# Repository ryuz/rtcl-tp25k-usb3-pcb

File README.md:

English version: [README_en.md](README_en.md)

# Tang Primer 25K 用 FT601 + MIPIコネクタ オリジナルベース基板

## 概要

Sipeed社の [Tang Primer 25K](https://wiki.sipeed.com/hardware/en/tang/tang-primer-25k/primer-25k.html) に搭載されている GW5A-LV25MG121 には MIPI D-PHY インターフェースが搭載されており、SoM までは配線が来ているようですが、残念ながら標準の Dock base board ではこのラインが未接続のままになっており、利用することができません。

本プロジェクトでは、MIPI D-PHY ラインを活用できるように 0.5mm ピッチ 22pin のコネクタに引き出したうえで、画像データなどを PC と交換できるように FT601 で USB3.0 接続できるオリジナルベース基板の設計データを提供します。

Tang Primer 25K の SoMボード でもともと使われていなかった MIPI ピンを利用するようにしていますが、特に MIPI を活用しなくとも、USB3.0 で FPGA を使えるようにしたボードとも言えますので、今まで FPGA と PC との接続で UART 程度で止まっていた人に本格的な FPGA 活用への第一歩として利用いただければ幸いです。

また、当方では試しておりませんが、GW5A-LV25MG121 の MIPI D-PHY は双方向ですので、MIPI-DSI など、表示系の実験にも利用できる可能性があります。

## スペック

主な実装内容は以下です。

- Tang-Primer25K-Core 取り付け用コネクタ
- FT601 による USB3.0 接続
- 4レーン MIPI コネクタ (22pin)
- PMOD コネクタ一個
- LED 4個
- プッシュスイッチ2個
- 2極ディップスイッチ
- JTAG 接続用 6pin ヘッダ

JTAG は外部に別途ダウンロードケーブルが必要ですが、[openFPGAloader](https://github.com/trabucayre/openFPGALoader)などを利用する場合は幅広いダウンロードケーブルが利用可能です。

また FT232HL などを利用する場合は、GOWIN EDA の GAO などを使ったデバッグも可能です。

## システムイメージ

### カメラ接続

[Raspberry PI V2 Camera](https://www.raspberrypi.com/documentation/accessories/camera.html) の接続例と、当方作の[RTCL-P3S7-MIPI](https://rtc-lab.com/products/rtcl-cam-p3s7-mipi/)の接続例です。

### JTAG接続

Digilent社の [JTAG-HS２](https://digilent.com/reference/programmers/jtag-hs2/start) の接続例と、秋月電子の[FT232HL ハイスピードUSBシリアル変換モジュール](https://akizukidenshi.com/catalog/g/g106503/) の接続例です。

## 設計データ

### 回路図

回路図は以下です。

- [rtcl-tp25k-usb3_v2.pdf](rtcl-tp25k-usb3_v2.pdf)

### KiCAD 設計データ

rtcl-tp25k-usb3 ディレクトリ以下に KiCAD 10.0 で設計したデータを格納しています。

JLCPCB の `JLC04161H-3313` で製造する想定で設計しています。

### ソフトウェア

下記にて開発中です。

https://github.com/ryuz/rtcl-designs/tree/main/projects/rtcl_tp25k_usb3

## 基板販売

当方で製造したものを[BOOTH](https://rtc-lab.booth.pm/) 及び [BASE](https://rtcl.base.shop/) にて販売中です。

詳細は下記をご覧ください。

https://rtc-lab.com/products/rtcl-design-rtcl_tp25k_usb3/

## 免責事項

本設計データは、研究開発用の試作実験に供するものであり、利用に際して発生した如何なる損害も作者は補償いたしませんので予めご了承ください。

また設計データについてもなんら品質を保証するものではありません。

## ライセンス(License)

本設計データは、[クリエイティブ・コモンズ 表示-非営利 4.0 国際 ライセンス(CC BY-NC 4.0)](https://creativecommons.org/licenses/by-nc/4.0/deed.ja)の下で提供されています。

製造した本基板の無断での販売や配布を行わない限りは、趣味や研究開発用途でご自由にお使いいただく事が出来ます。

また、商用に製造販売を希望される場合は、別途ライセンス契約を作者までご相談ください。[お問い合わせフォーム](https://rtc-lab.com/contact/)などからお問い合わせ頂けます。

## 作者情報

渕上 竜司(Ryuji Fuchikami)
[リアルタイムコンピューティング研究所](https://rtc-lab.com/)

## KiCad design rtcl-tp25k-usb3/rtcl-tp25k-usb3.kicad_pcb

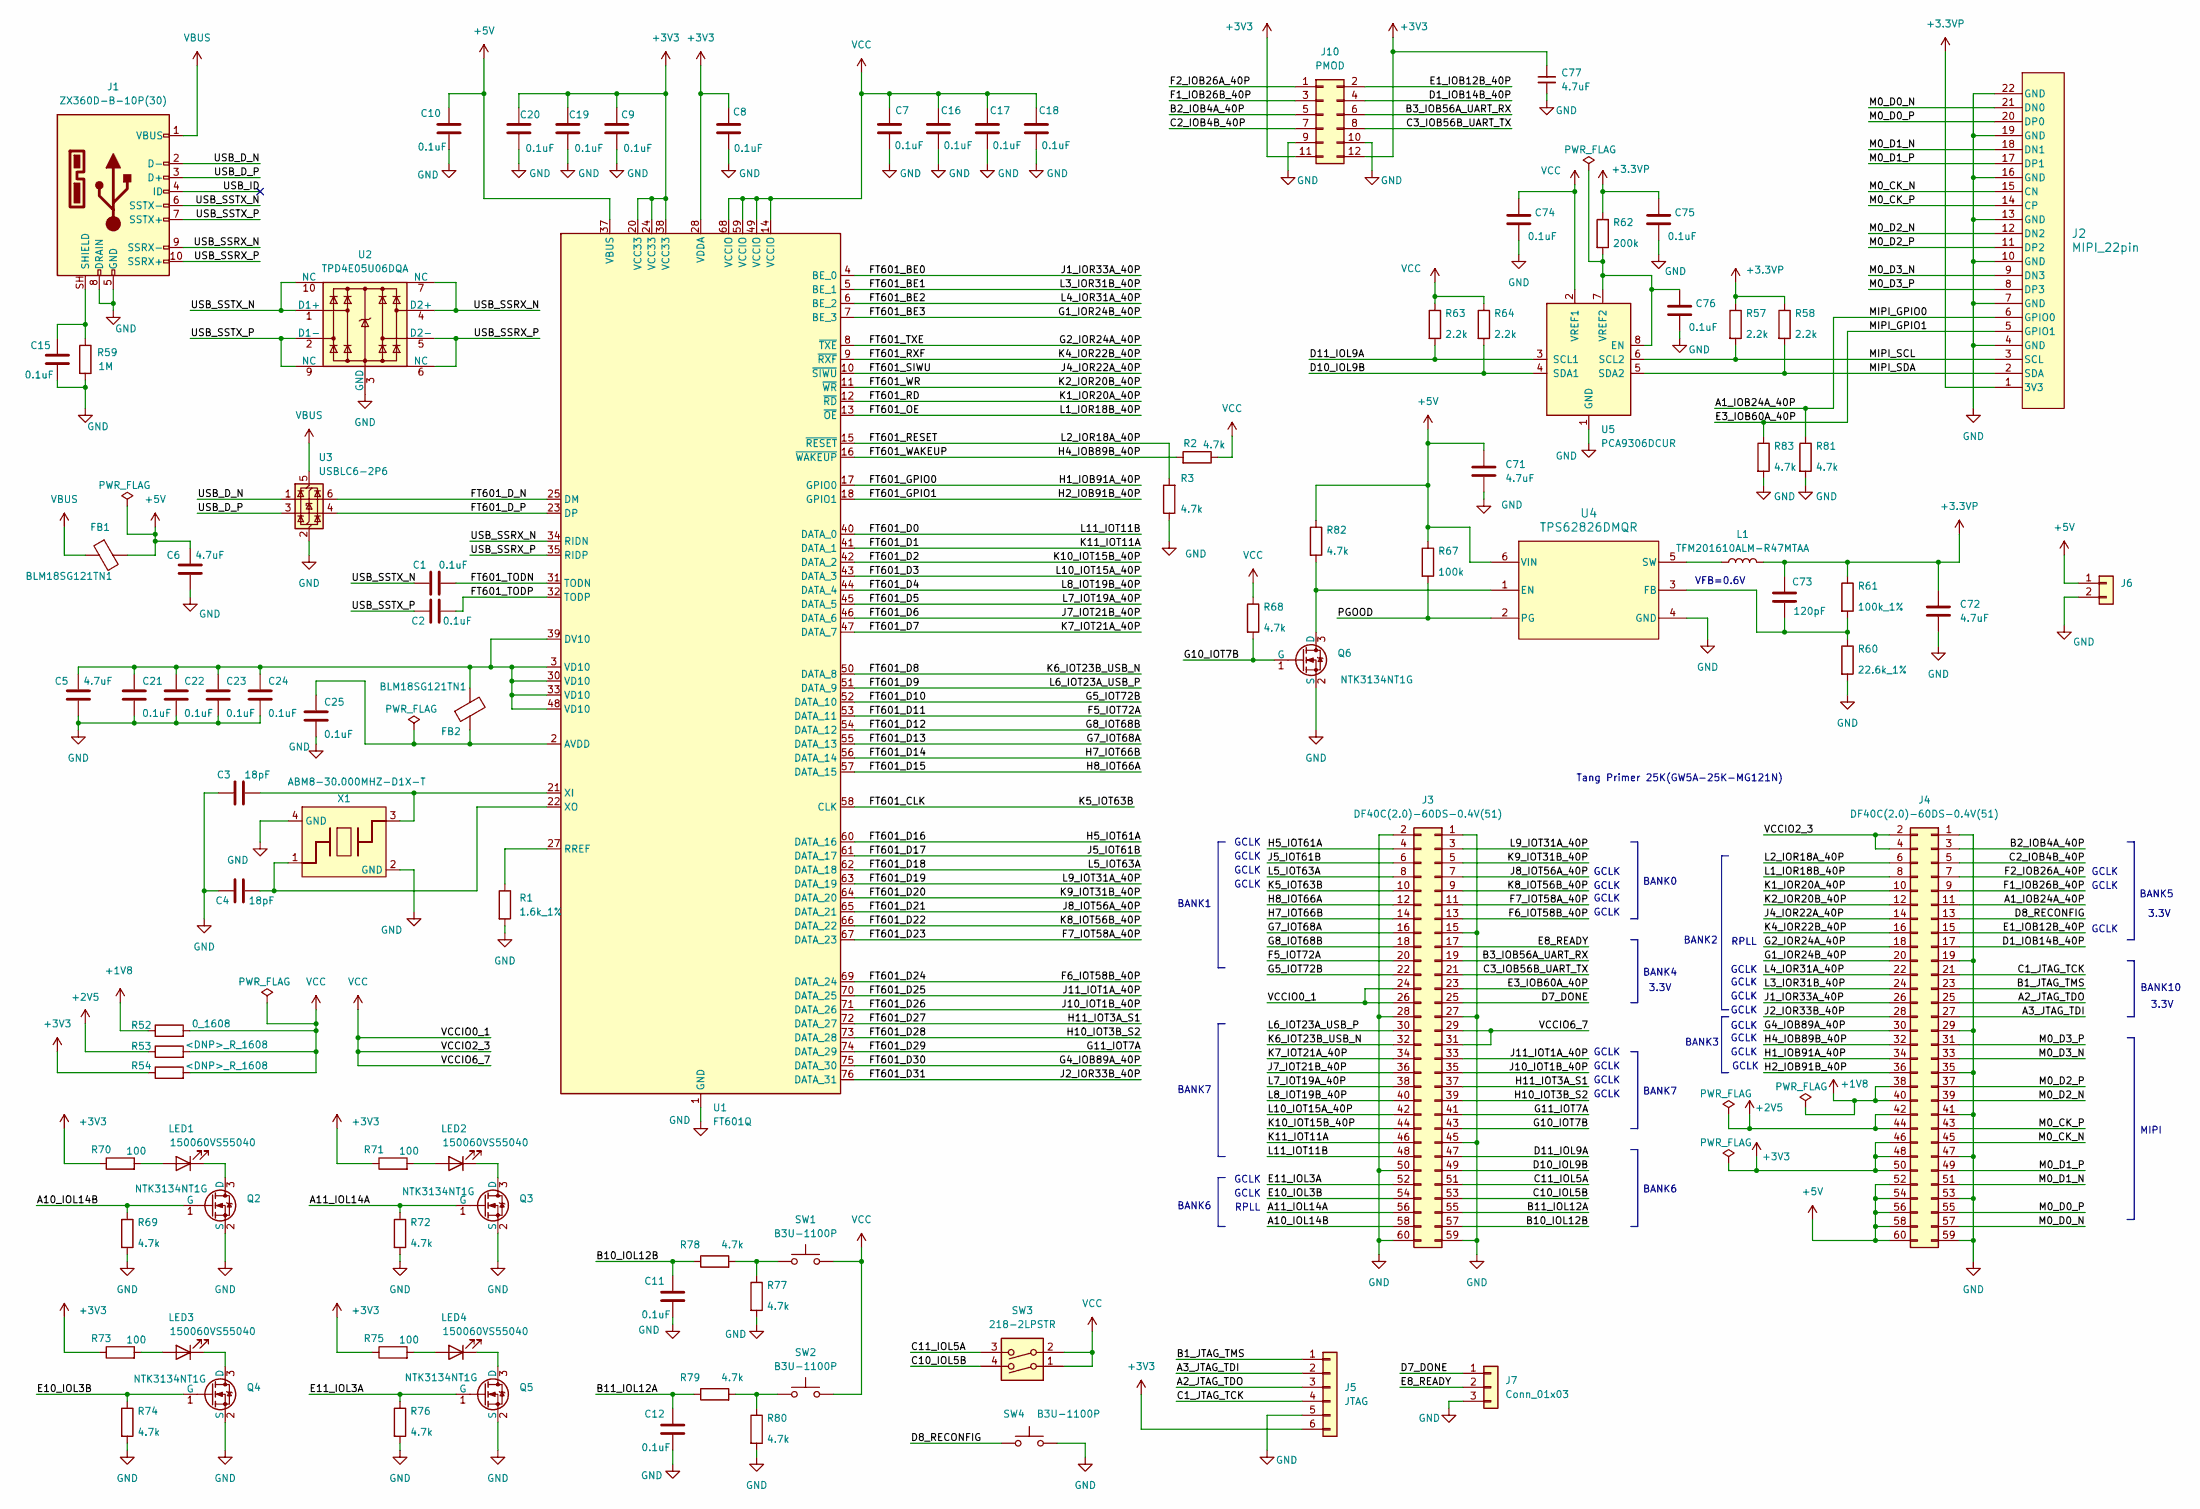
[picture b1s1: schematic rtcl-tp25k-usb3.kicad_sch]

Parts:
C1, C2, C7, C8, C9, C10, C11, C12, C15, C16, C17, C18, C19, C20, C21, C22, C23, C24, C25, C74, C75, C76: 0.1uF; C_0402_1005Metric
C3, C4: 18pF; C_0402_1005Metric
C5, C6, C71, C72, C77: 4.7uF; C_0603_1608Metric
C73: 120pF; C_0402_1005Metric; LCSC C40059
FB1, FB2: BLM18SG121TN1; L_0603_1608Metric; LCSC C113030
J1: ZX360D-B-10P(30); ZX360DB10P30; LCSC C598201
J2: MIPI_22pin; AFC11-S22ICA-00; LCSC C5248019
J3, J4: DF40C(2.0)-60DS-0.4V(51); CONN_DF40C-60DS_HIR; LCSC C3646124
J5: JTAG; PinHeader_1x06_P2.54mm_Vertical; LCSC C6332199
J6: Conn_01x02; PinHeader_1x02_P2.54mm_Vertical
J7: Conn_01x03; PinHeader_1x03_P2.54mm_Vertical
J10: PMOD; PMOD_02x06_2.54mm; LCSC C2897426
L1: TFM201610ALM-R47MTAA; INDC2016X100N; LCSC C501954
LED1, LED2, LED3, LED4: 150060VS55040; LED_0603_1608Metric; LCSC C6390388
Q2, Q3, Q4, Q5, Q6: NTK3134NT1G; SOT_34NT1G_ONS; Part 2SK3018; LCSC C97777
R1: 1.6k_1%; R_0402_1005Metric
R2, R3, R68, R69, R72, R74, R76, R77, R78, R79, R80, R81, R82, R83: 4.7k; R_0402_1005Metric
R52: 0_1608; R_0603_1608Metric_Pad0.98x0.95mm_HandSolder; LCSC C15402
R53, R54: <DNP>_R_1608; R_0603_1608Metric_Pad0.98x0.95mm_HandSolder
R57, R58, R63, R64: 2.2k; R_0402_1005Metric
R59: 1M; R_0402_1005Metric
R60: 22.6k_1%; R_0402_1005Metric
R61: 100k_1%; R_0402_1005Metric
R62: 200k; R_0402_1005Metric
R67: 100k; R_0402_1005Metric
R70, R71, R73, R75: 100; R_0402_1005Metric
SW1, SW2, SW4: B3U-1100P; LCSC C6467298
SW3: 218-2LPSTR; 218-2LP_CTS; LCSC C2961921
U1: FT601Q; QFN-76-1EP_9x9mm_P0.4mm_EP5.81x6.31mm; LCSC C1550513
U2: TPD4E05U06DQA; USON-10_2.5x1.0mm_P0.5mm; LCSC C138714
U3: USBLC6-2P6; SOT-666; LCSC C15999
U4: TPS62826DMQR; DMQ0006A; LCSC C2073319
U5: PCA9306DCUR; VSSOP-8_2.3x2mm_P0.5mm; LCSC C33196
X1: ABM8-30.000MHZ-D1X-T; XTAL_ABM8-30.000MHz-D1X-T; LCSC C1986781

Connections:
+1V8: J4.38, J4.40, R52.1
+2V5: J4.42, J4.44, R53.1
+3.3VP: C72.1, C73.1, C75.1, J2.1 (3V3), L1.2, R57.1, R58.1, R61.1, R62.1
+3V3: C8.2, C9.2, C19.2, C20.2, C77.1, J4.46, J4.48, J4.50, J5.6, J10.11, J10.12, R54.1, R70.1, R71.1, R73.1, R75.1, U1.20 (VCC33), U1.24 (VCC33), U1.28 (VDDA), U1.38 (VCC33)
+5V: C6.2, C10.2, C71.1, FB1.2, J4.52, J4.54, J4.56, J4.58, J4.60, J6.1, R67.1, R82.1, U1.37 (VBUS), U4.6 (VIN)
/A1_IOB24A_40P: J2.6 (GPIO0), J4.11, R81.1
/A2_JTAG_TDO: J4.25, J5.3
/A3_JTAG_TDI: J4.27, J5.2
/A10_IOL14B: J3.58, Q2.1 (G), R69.1
/A11_IOL14A: J3.56, Q3.1 (G), R72.1
/B1_JTAG_TMS: J4.23, J5.1
/B2_IOB4A_40P: J4.3, J10.5
/B3_IOB56A_UART_RX: J3.19, J10.6
/B10_IOL12B: C11.2, J3.57, R78.1
/B11_IOL12A: C12.2, J3.55, R79.1
/C1_JTAG_TCK: J4.21, J5.4
/C2_IOB4B_40P: J4.5, J10.7
/C3_IOB56B_UART_TX: J3.21, J10.8
/C10_IOL5B: J3.53, SW3.4
/C11_IOL5A: J3.51, SW3.3
/D1_IOB14B_40P: J4.17, J10.4
/D7_DONE: J3.25, J7.1
/D8_RECONFIG: J4.13, SW4.1
/D10_IOL9B: J3.49, R64.2, U5.4 (SDA1)
/D11_IOL9A: J3.47, R63.2, U5.3 (SCL1)
/E1_IOB12B_40P: J4.15, J10.2
/E3_IOB60A_40P: J2.5 (GPIO1), J3.23, R83.1
/E8_READY: J3.17, J7.2
/E10_IOL3B: J3.54, Q4.1 (G), R74.1
/E11_IOL3A: J3.52, Q5.1 (G), R76.1
/F1_IOB26B_40P: J4.9, J10.3
/F2_IOB26A_40P: J4.7, J10.1
/F5_IOT72A: J3.20, U1.53 (DATA_11)
/F6_IOT58B_40P: J3.13, U1.69 (DATA_24)
/F7_IOT58A_40P: J3.11, U1.67 (DATA_23)
/FT601_BE0: J4.26, U1.4 (BE_0)
/FT601_BE1: J4.24, U1.5 (BE_1)
/FT601_BE2: J4.22, U1.6 (BE_2)
/FT601_BE3: J4.20, U1.7 (BE_3)
/FT601_CLK: J3.10, U1.58 (CLK)
/FT601_D0: J3.48, U1.40 (DATA_0)
/FT601_D1: J3.46, U1.41 (DATA_1)
/FT601_D2: J3.44, U1.42 (DATA_2)
/FT601_D3: J3.42, U1.43 (DATA_3)
/FT601_D4: J3.40, U1.44 (DATA_4)
/FT601_D5: J3.38, U1.45 (DATA_5)
/FT601_D6: J3.36, U1.46 (DATA_6)
/FT601_D7: J3.34, U1.47 (DATA_7)
/FT601_D8: J3.32, U1.50 (DATA_8)
/FT601_D9: J3.30, U1.51 (DATA_9)
/FT601_D10: J3.22, U1.52 (DATA_10)
/FT601_D12: J3.18, U1.54 (DATA_12)
/FT601_D13: J3.16, U1.55 (DATA_13)
/FT601_D14: J3.14, U1.56 (DATA_14)
/FT601_D15: J3.12, U1.57 (DATA_15)
/FT601_D16: J3.4, U1.60 (DATA_16)
/FT601_D17: J3.6, U1.61 (DATA_17)
/FT601_D18: J3.8, U1.62 (DATA_18)
/FT601_D19: J3.3, U1.63 (DATA_19)
/FT601_D20: J3.5, U1.64 (DATA_20)
/FT601_D21: J3.7, U1.65 (DATA_21)
/FT601_D22: J3.9, U1.66 (DATA_22)
/FT601_D25: J3.33, U1.70 (DATA_25)
/FT601_D26: J3.35, U1.71 (DATA_26)
/FT601_D27: J3.37, U1.72 (DATA_27)
/FT601_D28: J3.39, U1.73 (DATA_28)
/FT601_D29: J3.41, U1.74 (DATA_29)
/FT601_D30: J4.30, U1.75 (DATA_30)
/FT601_D31: J4.28, U1.76 (DATA_31)
/FT601_D_N: U1.25 (DM), U3.6 (I/O1)
/FT601_D_P: U1.23 (DP), U3.4 (I/O2)
/FT601_GPIO0: J4.34, U1.17 (GPIO0)
/FT601_GPIO1: J4.36, U1.18 (GPIO1)
/FT601_OE: J4.8, U1.13 (~OE)
/FT601_RD: J4.10, U1.12 (~RD)
/FT601_RESET: J4.6, R3.2, U1.15 (~RESET)
/FT601_RXF: J4.16, U1.9 (~RXF)
/FT601_SIWU: J4.14, U1.10 (~SIWU)
/FT601_TODN: C1.2, U1.31 (TODN)
/FT601_TODP: C2.2, U1.32 (TODP)
/FT601_TXE: J4.18, U1.8 (~TXE)
/FT601_WAKEUP: J4.32, R2.2, U1.16 (~WAKEUP)
/FT601_WR: J4.12, U1.11 (~WR)
/G10_IOT7B: J3.43, Q6.1 (G), R68.2
/M0_CK_N: J2.15 (CN), J4.45
/M0_CK_P: J2.14 (CP), J4.43
/M0_D0_N: J2.21 (DN0), J4.57
/M0_D0_P: J2.20 (DP0), J4.55
/M0_D1_N: J2.18 (DN1), J4.51
/M0_D1_P: J2.17 (DP1), J4.49
/M0_D2_N: J2.12 (DN2), J4.39
/M0_D2_P: J2.11 (DP2), J4.37
/M0_D3_N: J2.9 (DN3), J4.33
/M0_D3_P: J2.8 (DP3), J4.31
/MIPI_SCL: J2.3 (SCL), R57.2, U5.6 (SCL2)
/MIPI_SDA: J2.2 (SDA), R58.2, U5.5 (SDA2)
/PGOOD: R67.2, U4.2 (PG)
/USB_D_N: J1.2 (D-), U3.1 (I/O1)
/USB_D_P: J1.3 (D+), U3.3 (I/O2)
/USB_ID: J1.4 (ID)
/USB_SSRX_N: J1.9 (SSRX-), U1.34 (RIDN), U2.4 (D2+), U2.7 (NC)
/USB_SSRX_P: J1.10 (SSRX+), U1.35 (RIDP), U2.5 (D2-), U2.6 (NC)
/USB_SSTX_N: C1.1, J1.6 (SSTX-), U2.1 (D1+), U2.10 (NC)
/USB_SSTX_P: C2.1, J1.7 (SSTX+), U2.2 (D1-), U2.9 (NC)
GND: C3.1, C4.1, C5.1, C6.1, C7.1, C8.1, C9.1, C10.1, C11.1, C12.1, C15.1, C16.1, C17.1, C18.1, C19.1, C20.1, C21.1, C22.1, C23.1, C24.1, C25.1, C71.2, C72.2, C74.2, C75.2, C76.2, C77.2, J1.5 (GND), J1.8 (DRAIN), J2.4 (GND), J2.7 (GND), J2.10 (GND), J2.13 (GND), J2.16 (GND), J2.19 (GND), J2.22 (GND), J3.1, J3.2, J3.15, J3.27, J3.28, J3.45, J3.50, J3.59, J3.60, J4.1, J4.19, J4.29, J4.35, J4.41, J4.47, J4.53, J4.59, J5.5, J6.2, J7.3, J10.9, J10.10, Q2.2 (S), Q3.2 (S), Q4.2 (S), Q5.2 (S), Q6.2 (S), R1.2, R3.1, R59.2, R60.2, R69.2, R72.2, R74.2, R76.2, R77.2, R80.2, R81.2, R83.2, SW4.2, U1.1 (GND), U1.26 (GND), U1.29 (GND), U1.36 (GND)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
unnamed: C15.2, J1.SH (SHIELD), R59.1
unnamed: LED1.2 (A), R70.2
unnamed: LED1.1 (K), Q2.3 (D)
unnamed: LED2.2 (A), R71.2
unnamed: LED2.1 (K), Q3.3 (D)
unnamed: LED3.2 (A), R73.2
unnamed: LED3.1 (K), Q4.3 (D)
unnamed: LED4.2 (A), R75.2
unnamed: LED4.1 (K), Q5.3 (D)
unnamed: Q6.3 (D), R82.2, U4.1 (EN)
unnamed: R77.1, R78.2, SW1.1
unnamed: R79.2, R80.1, SW2.1
unnamed: C25.2, FB2.1, U1.2 (AVDD)
unnamed: C5.2, C21.2, C22.2, C23.2, C24.2, FB2.2, U1.3 (VD10), U1.30 (VD10), U1.33 (VD10), U1.39 (DV10), U1.48 (VD10)
unnamed: R1.1, U1.27 (RREF)
unnamed: C3.2, U1.21 (XI), X1.3
unnamed: C4.2, U1.22 (XO), X1.1
unnamed: C73.2, R60.1, R61.2, U4.3 (FB)
unnamed: L1.1, U4.5 (SW)
unnamed: C76.1, R62.2, U5.7 (VREF2), U5.8 (EN)
VBUS: FB1.1, J1.1 (VBUS), U3.5 (VBUS)
VCC: C7.2, C16.2, C17.2, C18.2, C74.1, J3.24, J3.26, J3.29, J3.31, J4.2, J4.4, R2.1, R52.2, R53.2, R54.2, R63.1, R64.1, R68.1, SW1.2, SW2.2, SW3.1, SW3.2, U1.14 (VCCIO), U1.49 (VCCIO), U1.59 (VCCIO), U1.68 (VCCIO), U5.2 (VREF1)

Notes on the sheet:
GCLK
BANK7
BANK4
BANK7
VFB=0.6V
BANK6
RPLL
BANK2
3.3V
BANK0
Tang Primer 25K(GW5A-25K-MG121N)
BANK10
MIPI
BANK1
BANK5
BANK3
RPLL

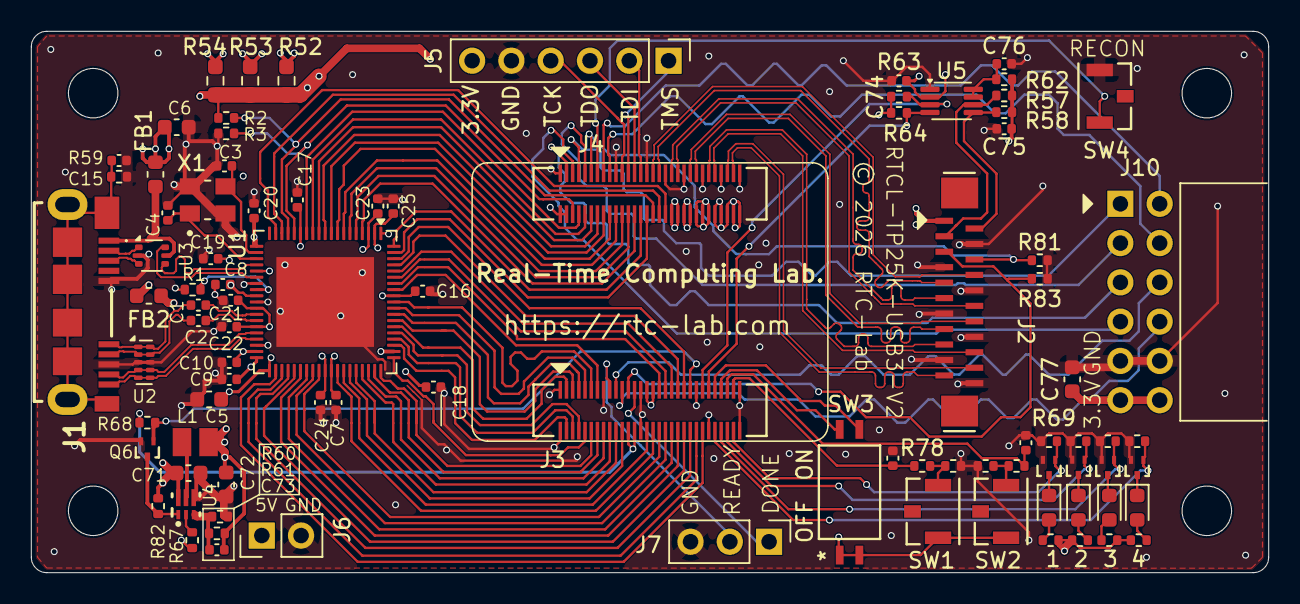
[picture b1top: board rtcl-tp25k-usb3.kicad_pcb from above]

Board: 4 copper layers, 80.0 x 35.0 mm, 91 parts (0 on the bottom side), 126 nets.

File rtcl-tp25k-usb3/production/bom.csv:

Designator,Footprint,Quantity,Value,LCSC Part #
"C1, C10, C11, C12, C15, C16, C17, C18, C19, C2, C20, C21, C22, C23, C24, C25, C7, C74, C75, C76, C8, C9",0402,22,0.1uF,
"C3, C4",0402,2,18pF,
"C5, C6, C71, C72, C77",0603,5,4.7uF,
C73,0402,1,120pF,C40059
"FB1, FB2",0603,2,BLM18SG121TN1,C113030
J1,ZX360DB10P30,1,ZX360D-B-10P(30),C598201
J10,PMOD_02x06_2.54mm,1,PMOD,C2897426
J2,AFC11-S22ICA-00,1,MIPI_22pin,C5248019
"J3, J4",CONN_DF40C-60DS_HIR,2,DF40C(2.0)-60DS-0.4V(51),C3646124
J5,PinHeader_1x06_P2.54mm_Vertical,1,JTAG,C6332199
J6,PinHeader_1x02_P2.54mm_Vertical,1,Conn_01x02,
J7,PinHeader_1x03_P2.54mm_Vertical,1,Conn_01x03,
L1,INDC2016X100N,1,TFM201610ALM-R47MTAA,C501954
"LED1, LED2, LED3, LED4",0603,4,150060VS55040,C6390388
"Q2, Q3, Q4, Q5, Q6",SOT_34NT1G_ONS,5,NTK3134NT1G,C97777
R1,0402,1,1.6k_1%,
"R2, R3, R68, R69, R72, R74, R76, R77, R78, R79, R80, R81, R82, R83",0402,14,4.7k,
R52,0603,1,0_1608,C15402
"R53, R54",0603,2,<DNP>_R_1608,
"R57, R58, R63, R64",0402,4,2.2k,
R59,0402,1,1M,
R60,0402,1,22.6k_1%,
R61,0402,1,100k_1%,
R62,0402,1,200k,
R67,0402,1,100k,
"R70, R71, R73, R75",0402,4,100,
"SW1, SW2, SW4",B3U-1100P,3,B3U-1100P,C6467298
SW3,218-2LP_CTS,1,218-2LPSTR,C2961921
U1,QFN-76-1EP_9x9mm_P0.4mm_EP5.81x6.31mm,1,FT601Q,C1550513
U2,USON-10_2.5x1.0mm_P0.5mm,1,TPD4E05U06DQA,C138714
U3,SOT-666,1,USBLC6-2P6,C15999
U4,DMQ0006A,1,TPS62826DMQR,C2073319
U5,VSSOP-8_2.3x2mm_P0.5mm,1,PCA9306DCUR,C33196
X1,XTAL_ABM8-30.000MHz-D1X-T,1,ABM8-30.000MHZ-D1X-T,C1986781

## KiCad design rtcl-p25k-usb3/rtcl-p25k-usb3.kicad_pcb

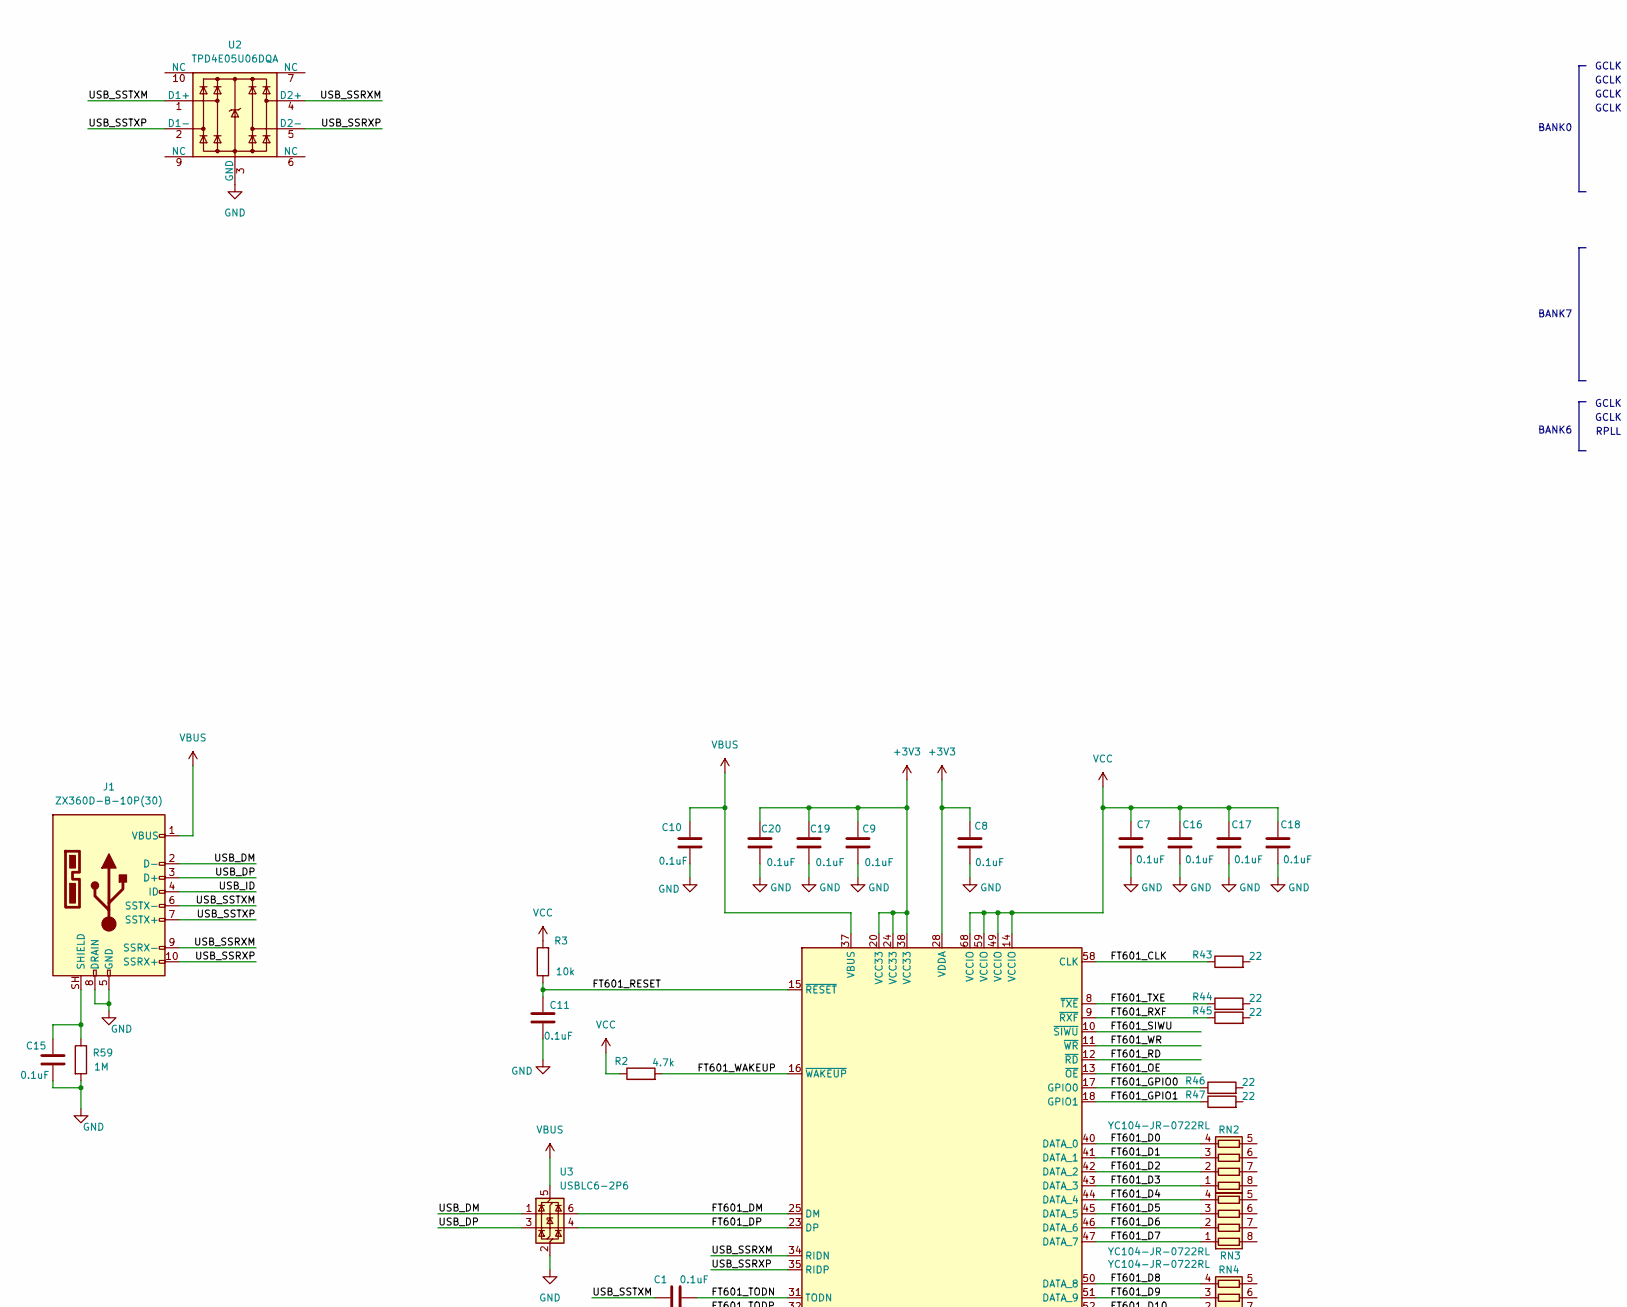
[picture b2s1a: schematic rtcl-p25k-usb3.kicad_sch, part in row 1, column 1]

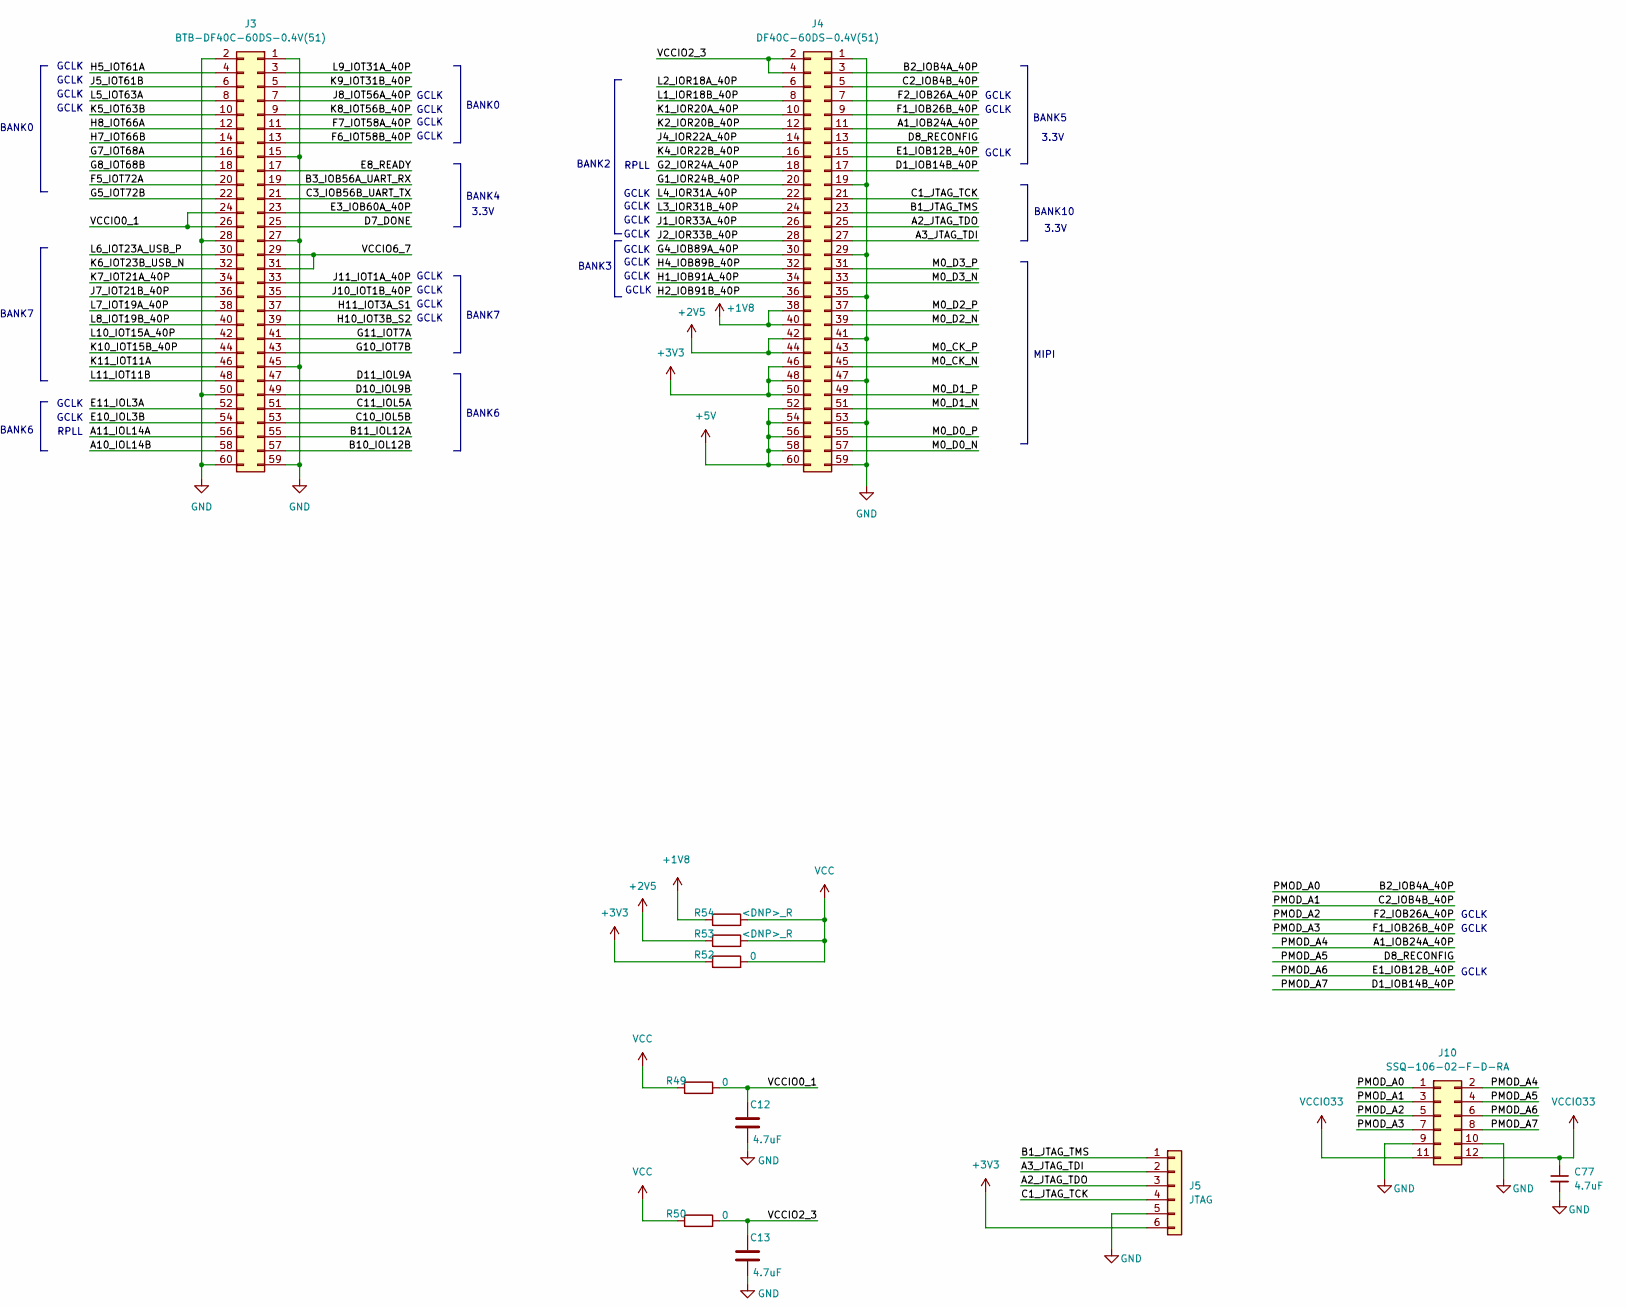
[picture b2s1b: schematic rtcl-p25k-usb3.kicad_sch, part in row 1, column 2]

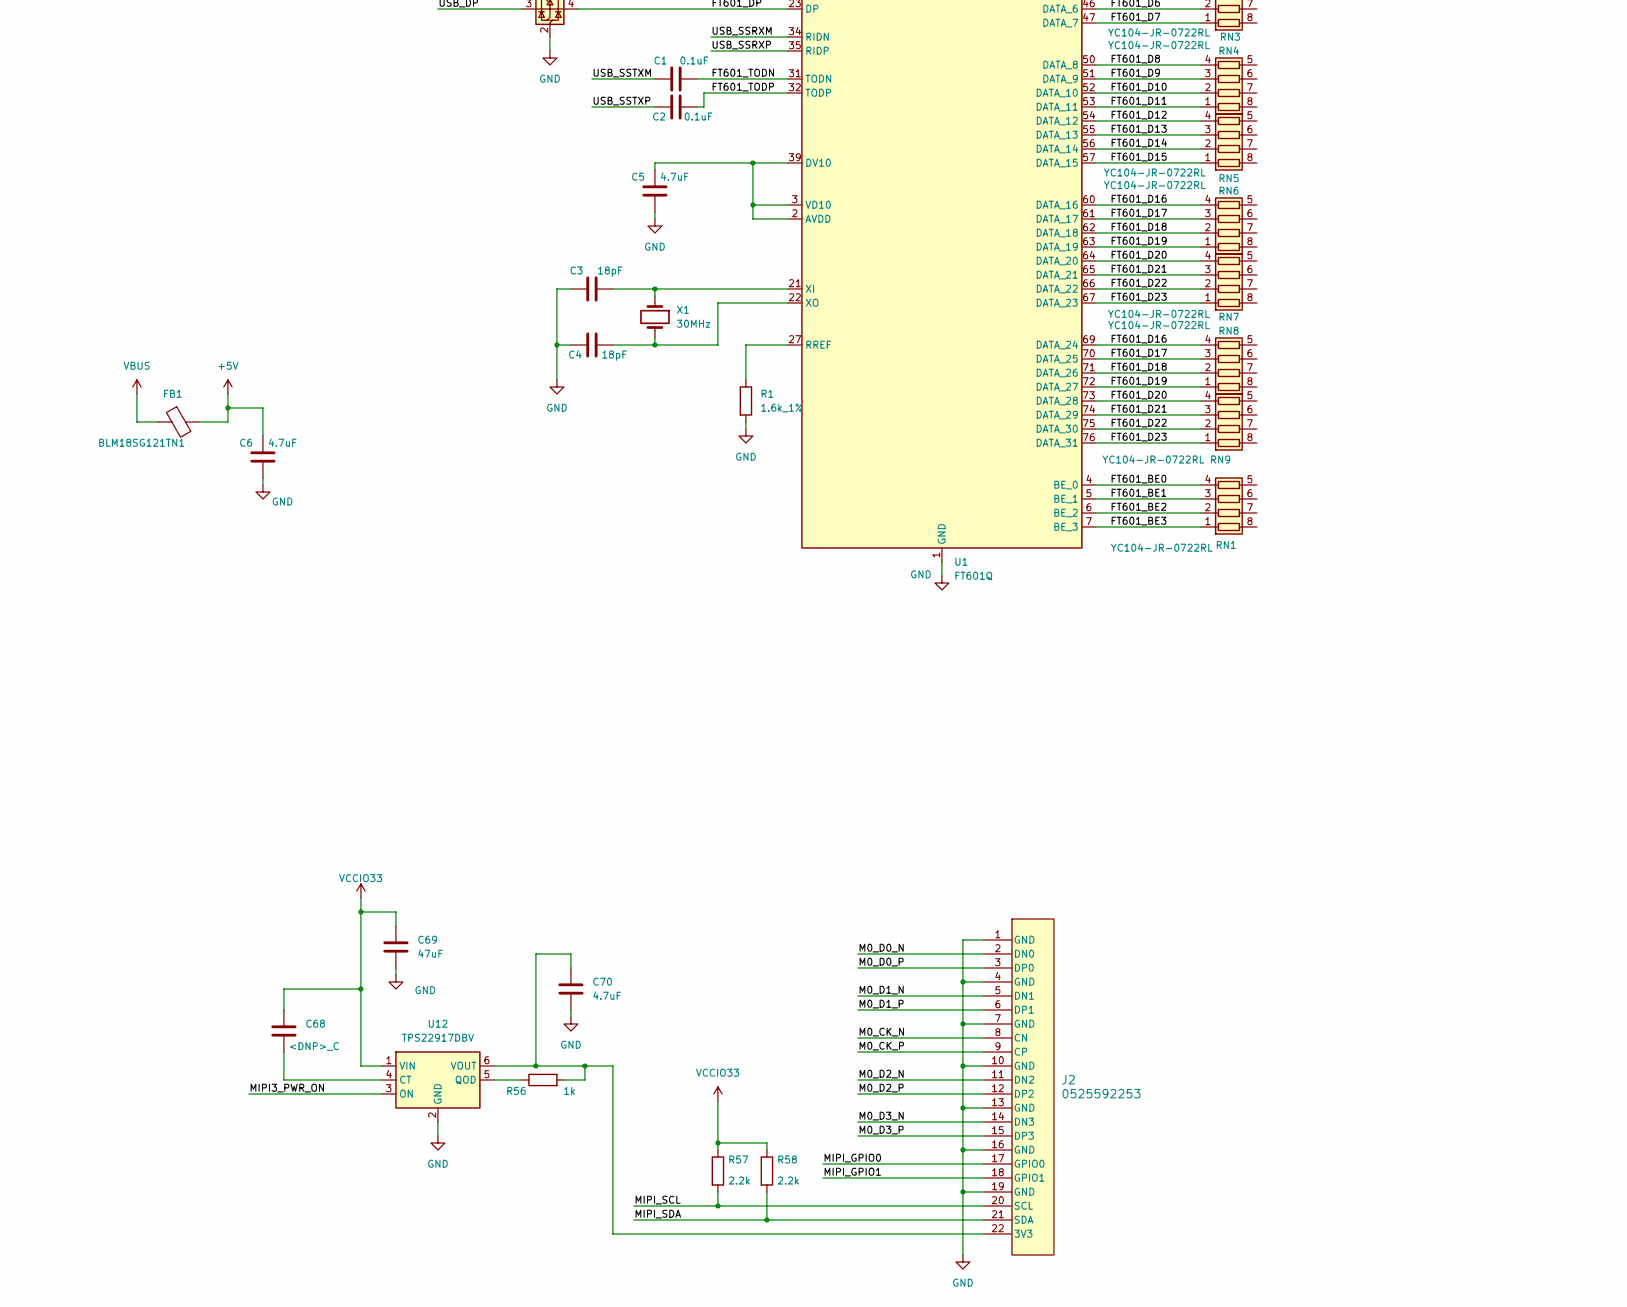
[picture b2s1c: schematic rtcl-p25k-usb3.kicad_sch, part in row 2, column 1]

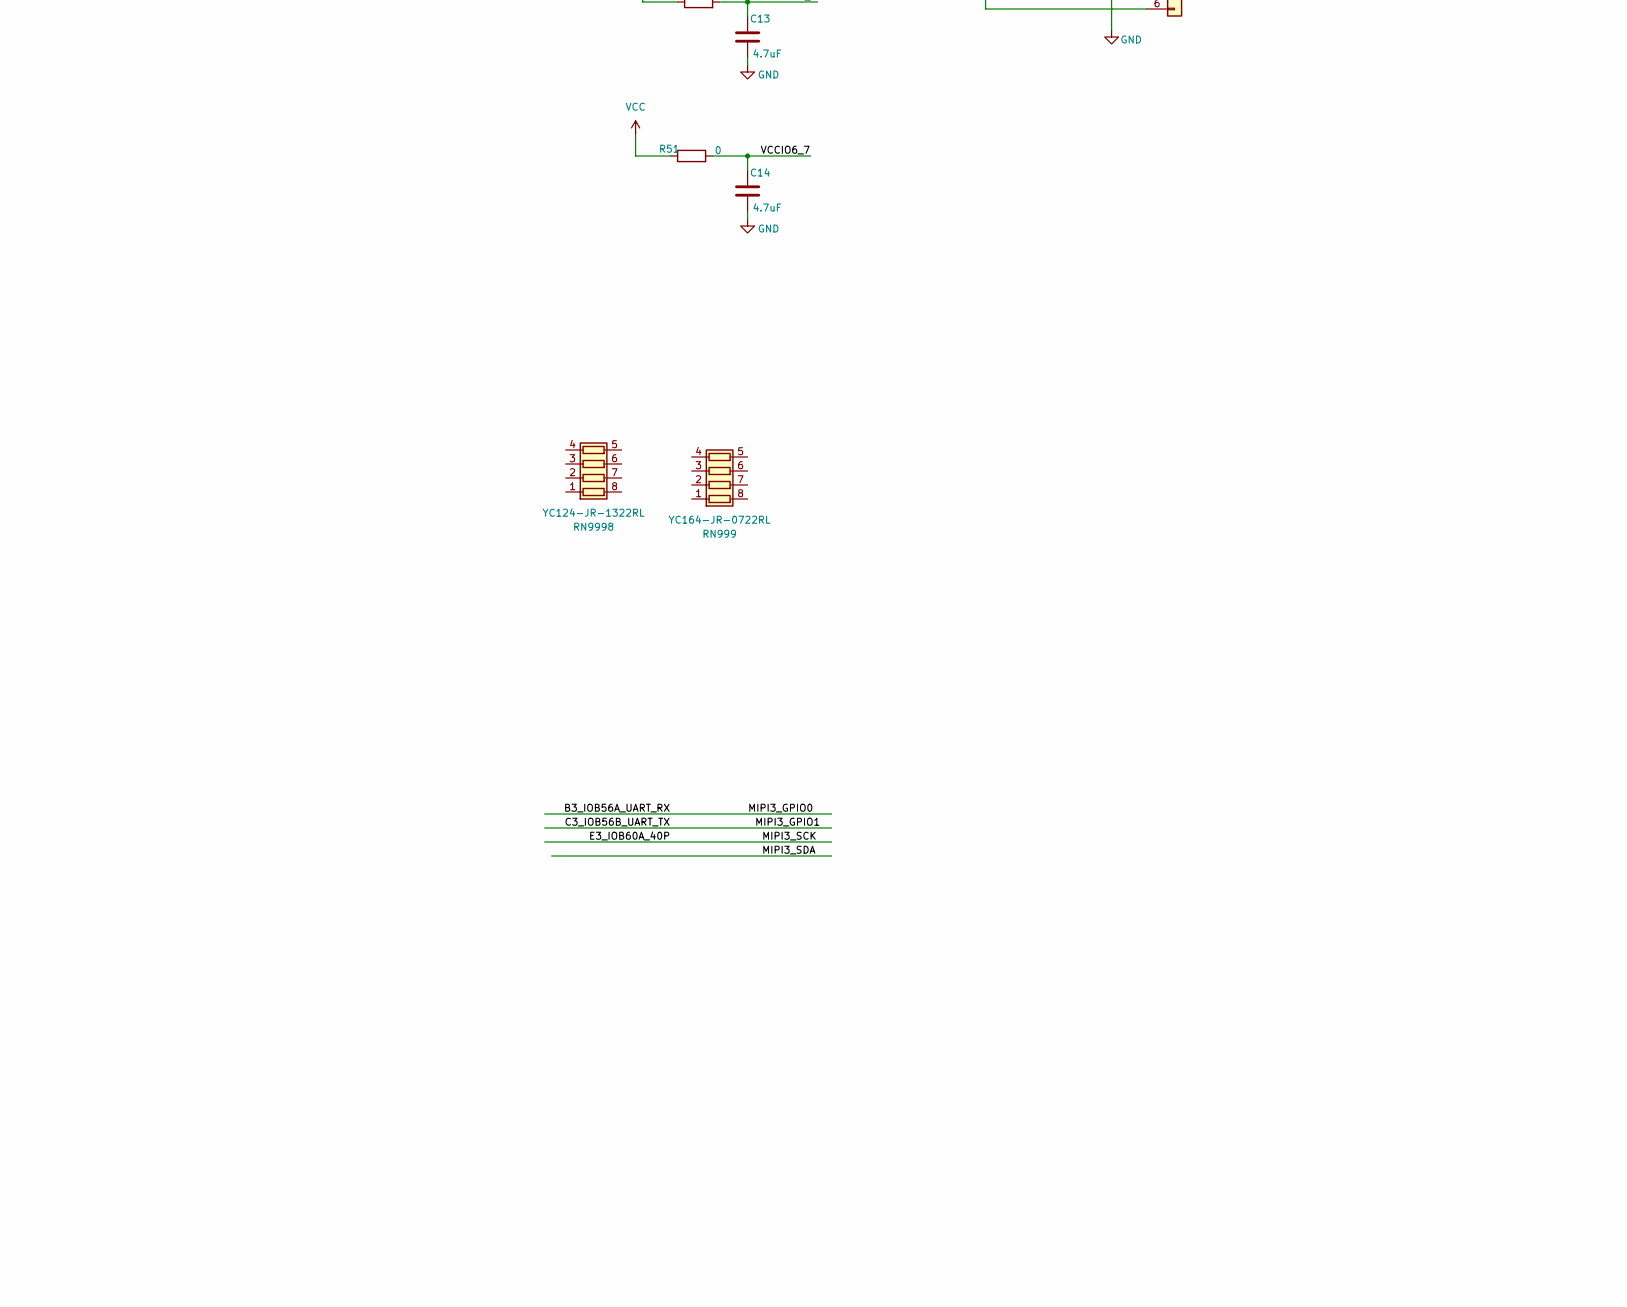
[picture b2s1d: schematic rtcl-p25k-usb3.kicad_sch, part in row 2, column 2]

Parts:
C1, C2, C7, C8, C9, C10, C11, C16, C17, C18, C19, C20: 0.1uF; C_0402_1005Metric
C3, C4: 18pF; C_0402_1005Metric
C5, C6, C12, C13, C14, C70: 4.7uF; C_0603_1608Metric
C15: 0.1uF; C_0603_1608Metric
C68: <DNP>_C; C_0603_1608Metric
C69: 47uF; C_0805_2012Metric
C77: 4.7uF; C_0402_1005Metric
FB1: BLM18SG121TN1
J1: ZX360D-B-10P(30); CONN10_ZX360D-B-10P30_HIR; LCSC C598201
J2: 0525592253; CON_525592253_MOL
J3: BTB-DF40C-60DS-0.4V(51); CONN_DF40C-60DS_HIR
J4: DF40C-60DS-0.4V(51); CONN_DF40C-60DS_HIR
J5: JTAG; PinHeader_1x06_P2.54mm_Vertical
J10: SSQ-106-02-F-D-RA; PMOD_02x06_2.54mm
R1: 1.6k_1%; R_0402_1005Metric
R2: 4.7k; R_0402_1005Metric
R3: 10k; R_0402_1005Metric
R43, R44, R45, R46, R47: 22; R_0402_1005Metric
R49, R50, R51, R52: 0; R_0402_1005Metric
R53, R54: <DNP>_R; R_0402_1005Metric
R56: 1k; R_0402_1005Metric
R57, R58: 2.2k; R_0402_1005Metric
R59: 1M; R_0402_1005Metric
RN1, RN2, RN3, RN4, RN5, RN6, RN7, RN8, RN9: YC104-JR-0722RL; RES_YC104_YAG
RN999: YC164-JR-0722RL; RES_YC164_3P2X1P6_YAG
RN9998: YC124-JR-1322RL; RES_YC164_3P2X1P6_YAG
U1: FT601Q; QFN-76-1EP_9x9mm_P0.4mm_EP5.81x6.31mm
U2: TPD4E05U06DQA; USON-10_2.5x1.0mm_P0.5mm
U3: USBLC6-2P6; SOT-666
U12: TPS22917DBV; SOT-23-6
X1: 30MHz

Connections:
+1V8: J4.38, J4.40, R54.1
+2V5: J4.42, J4.44, R53.1
+3V3: C8.2, C9.2, C19.2, C20.2, J4.46, J4.48, J4.50, J5.6, R52.1, U1.20 (VCC33), U1.24 (VCC33), U1.28 (VDDA), U1.38 (VCC33)
+5V: C6.2, FB1.2, J4.52, J4.54, J4.56, J4.58, J4.60
/A1_IOB24A_40P: J4.11, J10.2
/A2_JTAG_TDO: J4.25, J5.3
/A3_JTAG_TDI: J4.27, J5.2
/A10_IOL14B: J3.58
/A11_IOL14A: J3.56
/B1_JTAG_TMS: J4.23, J5.1
/B2_IOB4A_40P: J4.3, J10.1
/B3_IOB56A_UART_RX: J3.19
/B10_IOL12B: J3.57
/B11_IOL12A: J3.55
/C1_JTAG_TCK: J4.21, J5.4
/C2_IOB4B_40P: J4.5, J10.3
/C3_IOB56B_UART_TX: J3.21
/C10_IOL5B: J3.53
/C11_IOL5A: J3.51
/D1_IOB14B_40P: J4.17, J10.8
/D7_DONE: J3.25
/D8_RECONFIG: J4.13, J10.4
/D10_IOL9B: J3.49
/D11_IOL9A: J3.47
/E1_IOB12B_40P: J4.15, J10.6
/E3_IOB60A_40P: J3.23
/E8_READY: J3.17
/E10_IOL3B: J3.54
/E11_IOL3A: J3.52
/F1_IOB26B_40P: J4.9, J10.7
/F2_IOB26A_40P: J4.7, J10.5
/F5_IOT72A: J3.20
/F6_IOT58B_40P: J3.13
/F7_IOT58A_40P: J3.11
/FT601_BE0: RN1.4 (R4.1), U1.4 (BE_0)
/FT601_BE1: RN1.3 (R3.1), U1.5 (BE_1)
/FT601_BE2: RN1.2 (R2.1), U1.6 (BE_2)
/FT601_BE3: RN1.1 (R1.1), U1.7 (BE_3)
/FT601_CLK: R43.1, U1.58 (CLK)
/FT601_D0: RN2.4 (R4.1), U1.40 (DATA_0)
/FT601_D1: RN2.3 (R3.1), U1.41 (DATA_1)
/FT601_D2: RN2.2 (R2.1), U1.42 (DATA_2)
/FT601_D3: RN2.1 (R1.1), U1.43 (DATA_3)
/FT601_D4: RN3.4 (R4.1), U1.44 (DATA_4)
/FT601_D5: RN3.3 (R3.1), U1.45 (DATA_5)
/FT601_D6: RN3.2 (R2.1), U1.46 (DATA_6)
/FT601_D7: RN3.1 (R1.1), U1.47 (DATA_7)
/FT601_D8: RN4.4 (R4.1), U1.50 (DATA_8)
/FT601_D9: RN4.3 (R3.1), U1.51 (DATA_9)
/FT601_D10: RN4.2 (R2.1), U1.52 (DATA_10)
/FT601_D11: RN4.1 (R1.1), U1.53 (DATA_11)
/FT601_D12: RN5.4 (R4.1), U1.54 (DATA_12)
/FT601_D13: RN5.3 (R3.1), U1.55 (DATA_13)
/FT601_D14: RN5.2 (R2.1), U1.56 (DATA_14)
/FT601_D15: RN5.1 (R1.1), U1.57 (DATA_15)
/FT601_D16: RN6.4 (R4.1), RN8.4 (R4.1), U1.60 (DATA_16), U1.69 (DATA_24)
/FT601_D17: RN6.3 (R3.1), RN8.3 (R3.1), U1.61 (DATA_17), U1.70 (DATA_25)
/FT601_D18: RN6.2 (R2.1), RN8.2 (R2.1), U1.62 (DATA_18), U1.71 (DATA_26)
/FT601_D19: RN6.1 (R1.1), RN8.1 (R1.1), U1.63 (DATA_19), U1.72 (DATA_27)
/FT601_D20: RN7.4 (R4.1), RN9.4 (R4.1), U1.64 (DATA_20), U1.73 (DATA_28)
/FT601_D21: RN7.3 (R3.1), RN9.3 (R3.1), U1.65 (DATA_21), U1.74 (DATA_29)
/FT601_D22: RN7.2 (R2.1), RN9.2 (R2.1), U1.66 (DATA_22), U1.75 (DATA_30)
/FT601_D23: RN7.1 (R1.1), RN9.1 (R1.1), U1.67 (DATA_23), U1.76 (DATA_31)
/FT601_DM: U1.25 (DM), U3.6 (I/O1)
/FT601_DP: U1.23 (DP), U3.4 (I/O2)
/FT601_GPIO0: R46.1, U1.17 (GPIO0)
/FT601_GPIO1: R47.1, U1.18 (GPIO1)
/FT601_OE: U1.13 (~OE)
/FT601_RD: U1.12 (~RD)
/FT601_RESET: C11.2, R3.1, U1.15 (~RESET)
/FT601_RXF: R45.1, U1.9 (~RXF)
/FT601_SIWU: U1.10 (~SIWU)
/FT601_TODN: C1.2, U1.31 (TODN)
/FT601_TODP: C2.2, U1.32 (TODP)
/FT601_TXE: R44.1, U1.8 (~TXE)
/FT601_WAKEUP: R2.2, U1.16 (~WAKEUP)
/FT601_WR: U1.11 (~WR)
/G1_IOR24B_40P: J4.20
/G2_IOR24A_40P: J4.18
/G4_IOB89A_40P: J4.30
/G5_IOT72B: J3.22
/G7_IOT68A: J3.16
/G8_IOT68B: J3.18
/G10_IOT7B: J3.43
/G11_IOT7A: J3.41
/H1_IOB91A_40P: J4.34
/H2_IOB91B_40P: J4.36
/H4_IOB89B_40P: J4.32
/H5_IOT61A: J3.4
/H7_IOT66B: J3.14
/H8_IOT66A: J3.12
/H10_IOT3B_S2: J3.39
/H11_IOT3A_S1: J3.37
/J1_IOR33A_40P: J4.26
/J2_IOR33B_40P: J4.28
/J4_IOR22A_40P: J4.14
/J5_IOT61B: J3.6
/J7_IOT21B_40P: J3.36
/J8_IOT56A_40P: J3.7
/J10_IOT1B_40P: J3.35
/J11_IOT1A_40P: J3.33
/K1_IOR20A_40P: J4.10
/K2_IOR20B_40P: J4.12
/K4_IOR22B_40P: J4.16
/K5_IOT63B: J3.10
/K6_IOT23B_USB_N: J3.32
/K7_IOT21A_40P: J3.34
/K8_IOT56B_40P: J3.9
/K9_IOT31B_40P: J3.5
/K10_IOT15B_40P: J3.44
/K11_IOT11A: J3.46
/L1_IOR18B_40P: J4.8
/L2_IOR18A_40P: J4.6
/L3_IOR31B_40P: J4.24
/L4_IOR31A_40P: J4.22
/L5_IOT63A: J3.8
/L6_IOT23A_USB_P: J3.30
/L7_IOT19A_40P: J3.38
/L8_IOT19B_40P: J3.40
/L9_IOT31A_40P: J3.3
/L10_IOT15A_40P: J3.42
/L11_IOT11B: J3.48
/M0_CK_N: J2.8 (CN), J4.45
/M0_CK_P: J2.9 (CP), J4.43
/M0_D0_N: J2.2 (DN0), J4.57
/M0_D0_P: J2.3 (DP0), J4.55
/M0_D1_N: J2.5 (DN1), J4.51
/M0_D1_P: J2.6 (DP1), J4.49
/M0_D2_N: J2.11 (DN2), J4.39
/M0_D2_P: J2.12 (DP2), J4.37
/M0_D3_N: J2.14 (DN3), J4.33
/M0_D3_P: J2.15 (DP3), J4.31
/MIPI3_PWR_ON: U12.3 (ON)
/MIPI_GPIO0: J2.17 (GPIO0)
/MIPI_GPIO1: J2.18 (GPIO1)
/MIPI_SCL: J2.20 (SCL), R57.2
/MIPI_SDA: J2.21 (SDA), R58.2
/USB_DM: J1.2 (D-), U3.1 (I/O1)
/USB_DP: J1.3 (D+), U3.3 (I/O2)
/USB_ID: J1.4 (ID)
/USB_SSRXM: J1.9 (SSRX-), U1.34 (RIDN), U2.4 (D2+)
/USB_SSRXP: J1.10 (SSRX+), U1.35 (RIDP), U2.5 (D2-)
/USB_SSTXM: C1.1, J1.6 (SSTX-), U2.1 (D1+)
/USB_SSTXP: C2.1, J1.7 (SSTX+), U2.2 (D1-)
/VCCIO0_1: C12.2, J3.24, J3.26, R49.2
/VCCIO2_3: C13.2, J4.2, J4.4, R50.2
/VCCIO6_7: C14.2, J3.29, J3.31, R51.2
GND: C3.1, C4.1, C5.1, C6.1, C7.1, C8.1, C9.1, C10.1, C11.1, C12.1, C13.1, C14.1, C15.1, C16.1, C17.1, C18.1, C19.1, C20.1, C69.2, C70.2, C77.2, J1.5 (GND), J1.8 (DRAIN), J2.1 (GND), J2.4 (GND), J2.7 (GND), J2.10 (GND), J2.13 (GND), J2.16 (GND), J2.19 (GND), J3.1, J3.2, J3.15, J3.27, J3.28, J3.45, J3.50, J3.59, J3.60, J4.1, J4.19, J4.29, J4.35, J4.41, J4.47, J4.53, J4.59, J5.5, J10.9, J10.10, R1.2, R59.2, U1.1 (GND), U1.26 (GND), U1.29 (GND), U1.36 (GND), U1.77 (GND), U2.3 (GND), U2.8 (GND), U3.2 (GND), U12.2 (GND)
unnamed: C15.2, J1.SH (SHIELD), R59.1
unnamed: C70.1, J2.22 (3V3), R56.2, U12.6 (VOUT)
unnamed: C5.2, U1.2 (AVDD), U1.3 (VD10), U1.30 (VD10), U1.33 (VD10), U1.39 (DV10), U1.48 (VD10)
unnamed: R1.1, U1.27 (RREF)
unnamed: C3.2, U1.21 (XI), X1.1
unnamed: C4.2, U1.22 (XO), X1.2
unnamed: C68.2, U12.4 (CT)
unnamed: R56.1, U12.5 (QOD)
VBUS: C10.2, FB1.1, J1.1 (VBUS), U1.37 (VBUS), U3.5 (VBUS)
VCC: C7.2, C16.2, C17.2, C18.2, R2.1, R3.2, R49.1, R50.1, R51.1, R52.2, R53.2, R54.2, U1.14 (VCCIO), U1.49 (VCCIO), U1.59 (VCCIO), U1.68 (VCCIO)
VCCIO33: C68.1, C69.1, C77.1, J10.11, J10.12, R57.1, R58.1, U12.1 (VIN)

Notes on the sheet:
GCLK
BANK7
BANK4
BANK7
BANK6
RPLL
BANK2
3.3V
BANK0
BANK10
MIPI
BANK5
BANK3
RPLL

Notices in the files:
rtcl-tp25k-usb3/rtcl-tp25k-usb3.kicad_pcb:
© 2026 RTC-Lab
parts and their libraries:
Copyright 2016 Accelerated Designs. All rights reserved.
